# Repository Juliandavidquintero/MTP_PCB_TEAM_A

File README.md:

References:
- Connecting power button:                  https://howchoo.com/pi/how-to-add-a-power-button-to-your-raspberry-pi/
- Connecting decoupling capacitor:          https://www.mysensors.org/build/connect_radio
- Connections between module and Raspi:     https://forum.mysensors.org/topic/2437/step-by-step-procedure-to-connect-the-nrf24l01-to-the-gpio-pins-and-use-the-raspberry-as-a-serial-gateway-mysensors-1-x
                                            https://lastminuteengineers.com/nrf24l01-arduino-wireless-communication/

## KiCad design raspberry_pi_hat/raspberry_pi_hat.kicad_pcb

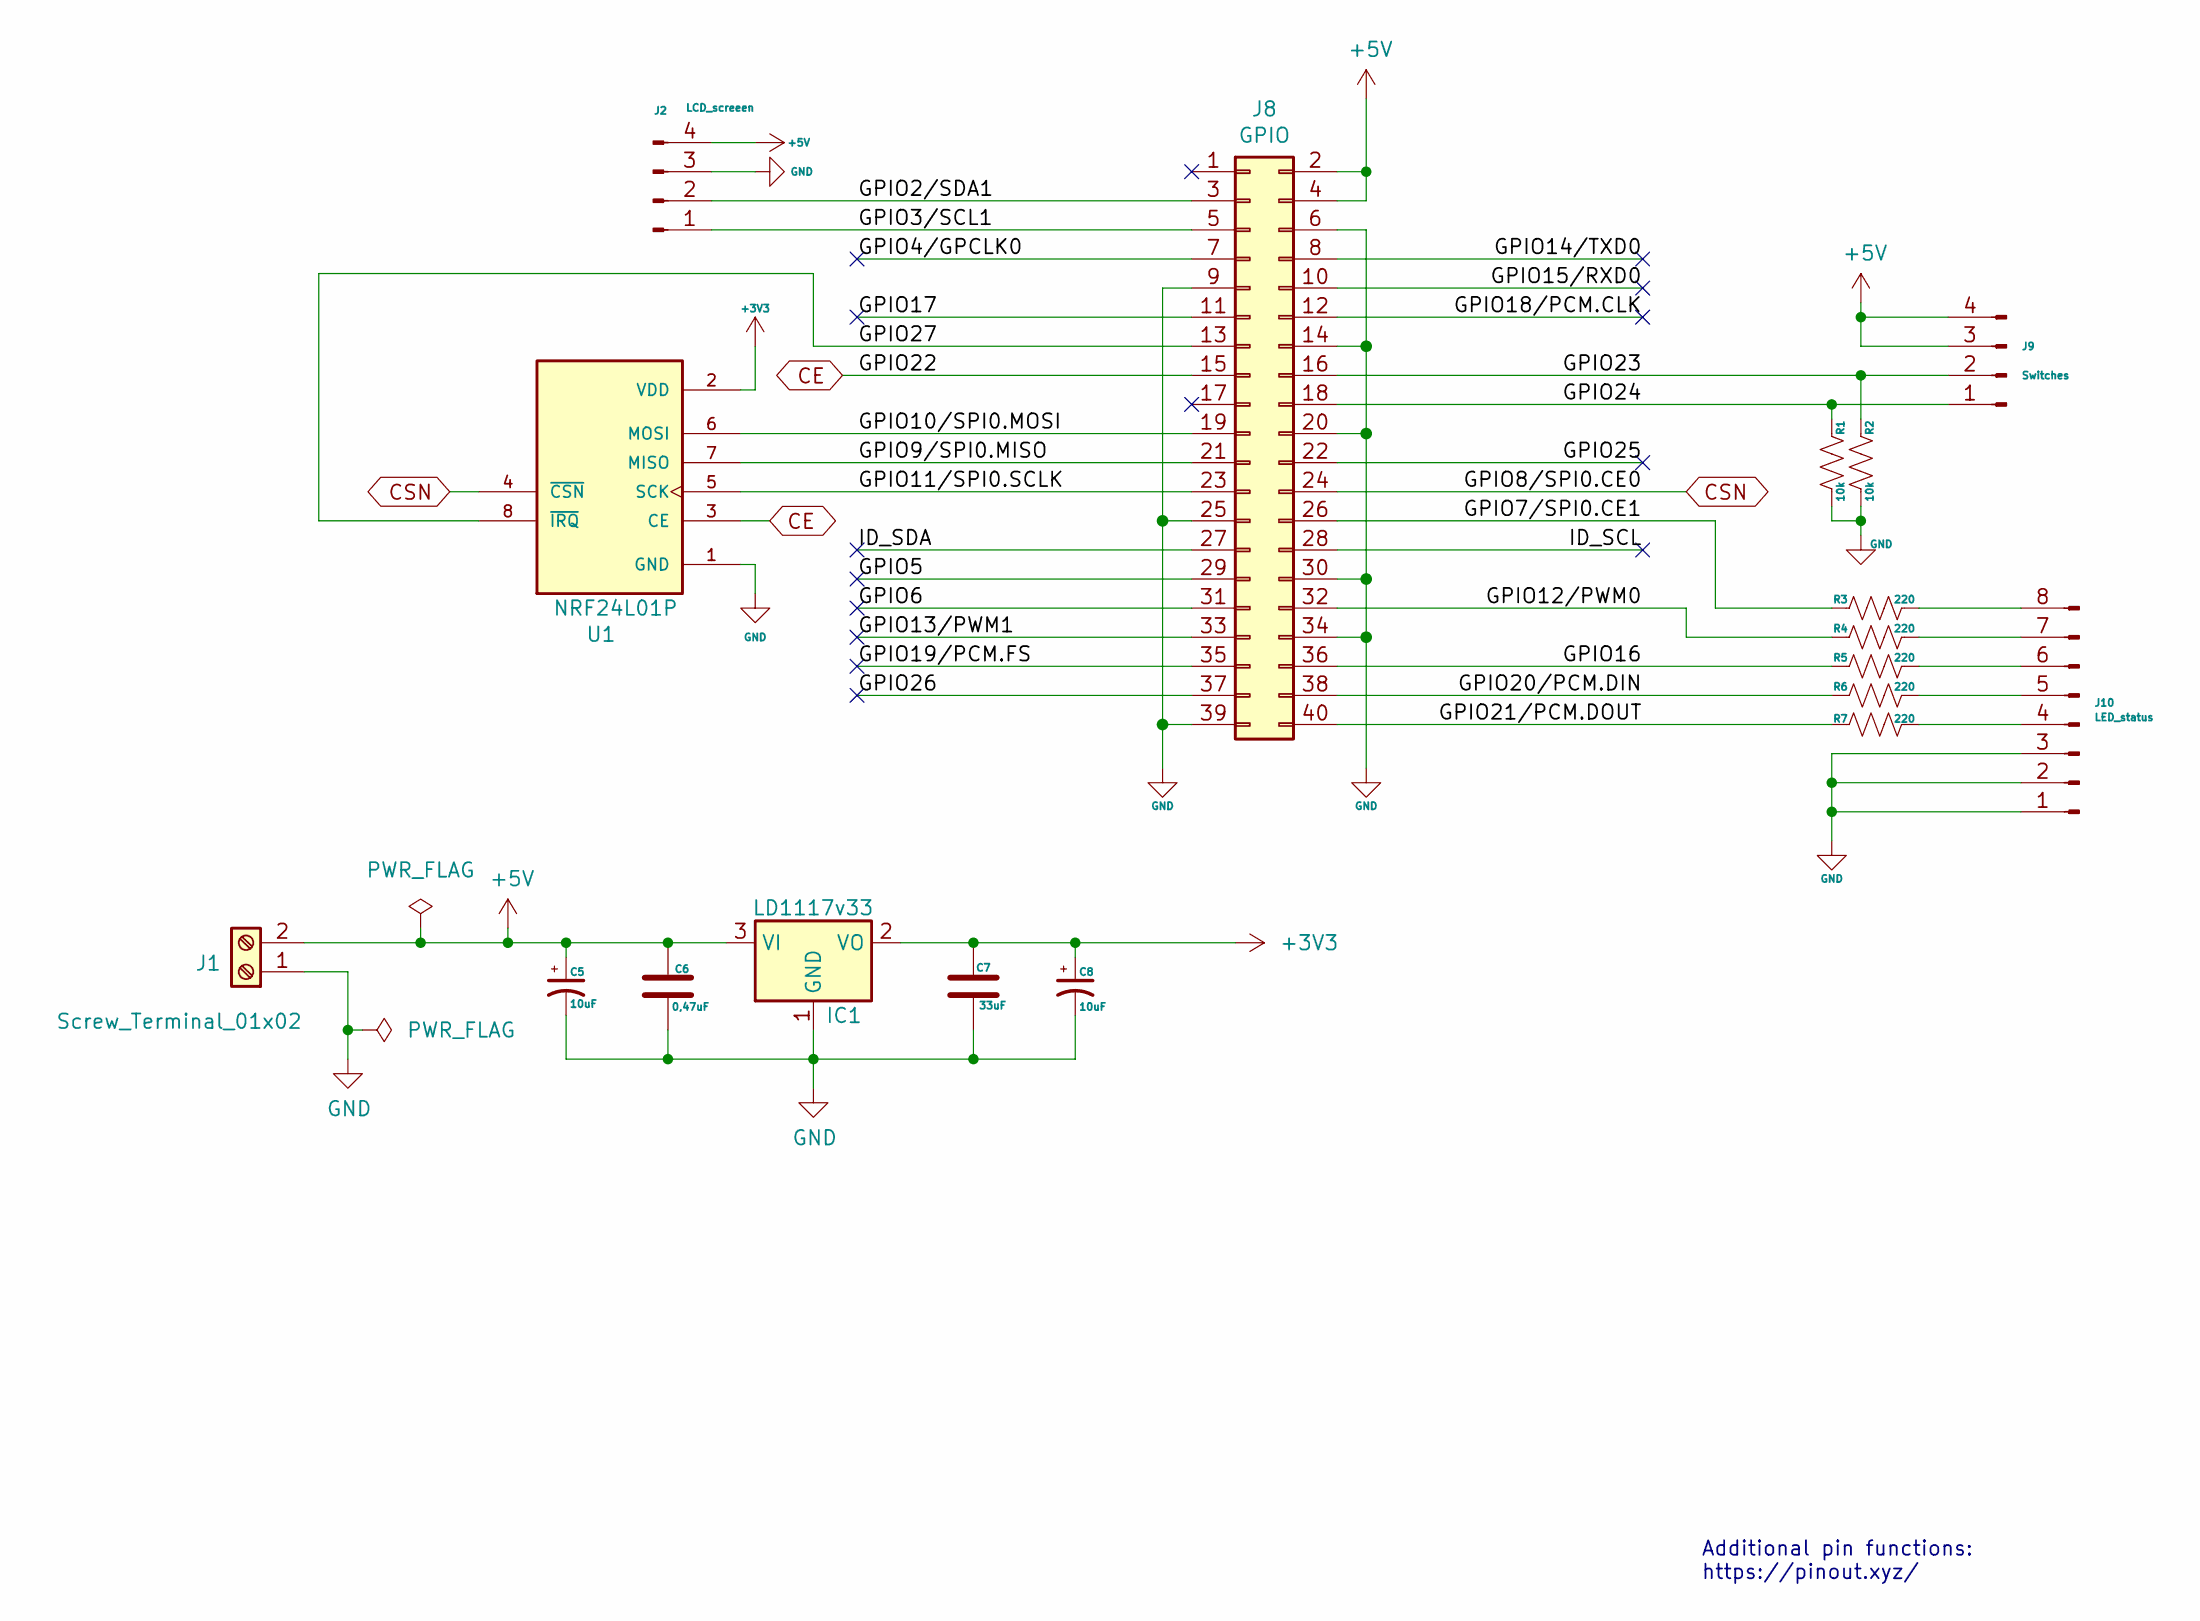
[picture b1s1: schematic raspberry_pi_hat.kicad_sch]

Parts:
C5, C8: 10uF; CP_Radial_D5.0mm_P2.50mm
C6: 0,47uF; C_Radial_D4.0mm_H5.0mm_P1.50mm
C7: 33uF; C_Radial_D4.0mm_H5.0mm_P1.50mm
IC1: LD1117v33; TO-220-3_Vertical; Mouser Part Number 926-LM3940IT-3.3NOPB
J1: Screw_Terminal_01x02; TerminalBlock_MetzConnect_Type101_RT01602HBWC_1x02_P5.08mm_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
J2: LCD_screeen; Molex_KK-254_AE-6410-04A_1x04_P2.54mm_Vertical
J8: GPIO; Raspberry_Pi_Zero_Socketed_THT_FaceDown_MountingHoles
J9: Switches; Molex_KK-254_AE-6410-04A_1x04_P2.54mm_Vertical
J10: LED_status; Molex_KK-254_AE-6410-08A_1x08_P2.54mm_Vertical
R1, R2: 10k; R_Axial_DIN0309_L9.0mm_D3.2mm_P12.70mm_Horizontal
R3, R4, R5, R6, R7: 220; R_Axial_DIN0309_L9.0mm_D3.2mm_P12.70mm_Horizontal
U1: NRF24L01P; XCVR_NRF24L01P-MODULE-PCB

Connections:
+3V3: C7.1, C8.1, IC1.2 (VO), U1.2 (VDD)
+5V: C5.1, C6.1, IC1.3 (VI), J1.2, J2.4, J8.2, J8.4, J9.3, J9.4
/GPIO2/SDA1: J2.2, J8.3
/GPIO3/SCL1: J2.1, J8.5
/GPIO4/GPCLK0: J8.7
/GPIO5: J8.29
/GPIO6: J8.31
/GPIO7/SPI0.CE1: J8.26, R3.1
/GPIO9/SPI0.MISO: J8.21, U1.7 (MISO)
/GPIO10/SPI0.MOSI: J8.19, U1.6 (MOSI)
/GPIO11/SPI0.SCLK: J8.23, U1.5 (SCK)
/GPIO12/PWM0: J8.32, R4.1
/GPIO13/PWM1: J8.33
/GPIO14/TXD0: J8.8
/GPIO15/RXD0: J8.10
/GPIO16: J8.36, R5.1
/GPIO17: J8.11
/GPIO18/PCM.CLK: J8.12
/GPIO19/PCM.FS: J8.35
/GPIO20/PCM.DIN: J8.38, R6.1
/GPIO21/PCM.DOUT: J8.40, R7.1
/GPIO23: J8.16, J9.2, R2.1
/GPIO24: J8.18, J9.1, R1.1
/GPIO25: J8.22
/GPIO26: J8.37
/GPIO27: J8.13, U1.8 (~IRQ)
/ID_SCL: J8.28
/ID_SDA: J8.27
CE: J8.15, U1.3 (CE)
CSN: J8.24, U1.4 (~CSN)
GND: C5.2, C6.2, C7.2, C8.2, IC1.1 (GND), J1.1, J2.3, J8.6, J8.9, J8.14, J8.20, J8.25, J8.30, J8.34, J8.39, J10.1, J10.2, J10.3, R1.2, R2.2, U1.1 (GND)
unnamed: J10.4, R7.2
unnamed: J10.5, R6.2
unnamed: J10.6, R5.2
unnamed: J10.7, R4.2
unnamed: J10.8, R3.2

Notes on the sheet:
Additional pin functions: https://pinout.xyz/

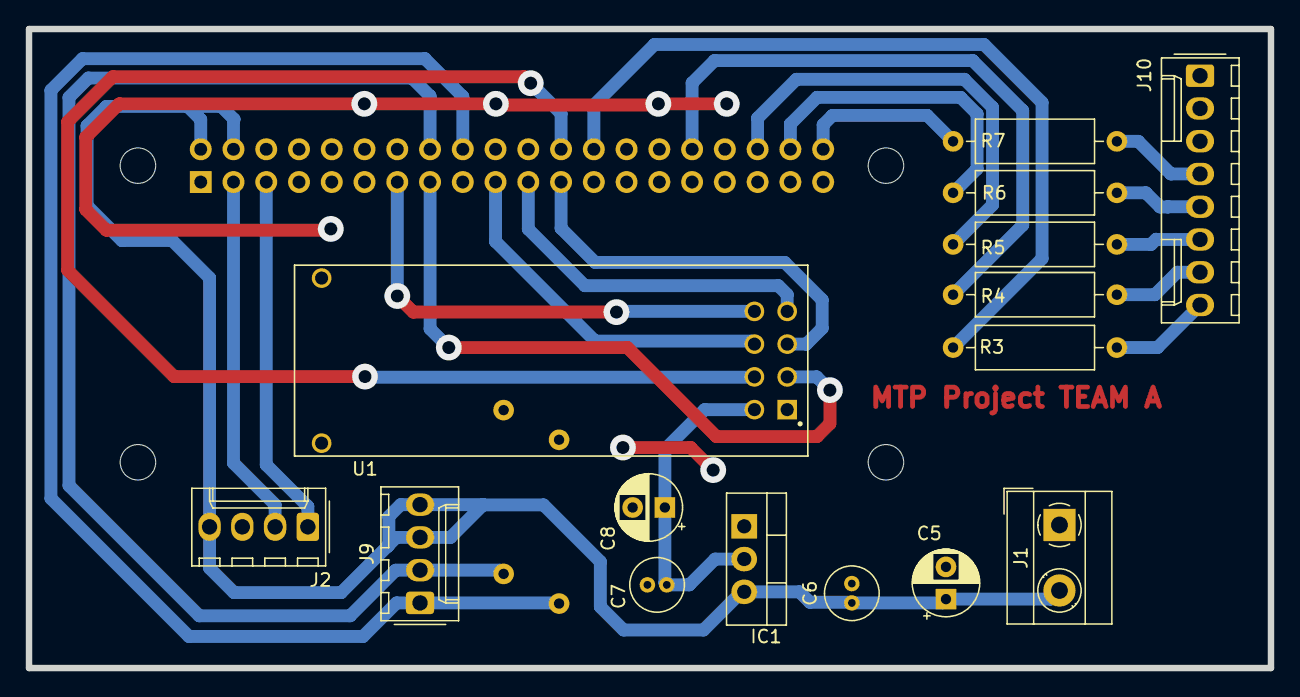
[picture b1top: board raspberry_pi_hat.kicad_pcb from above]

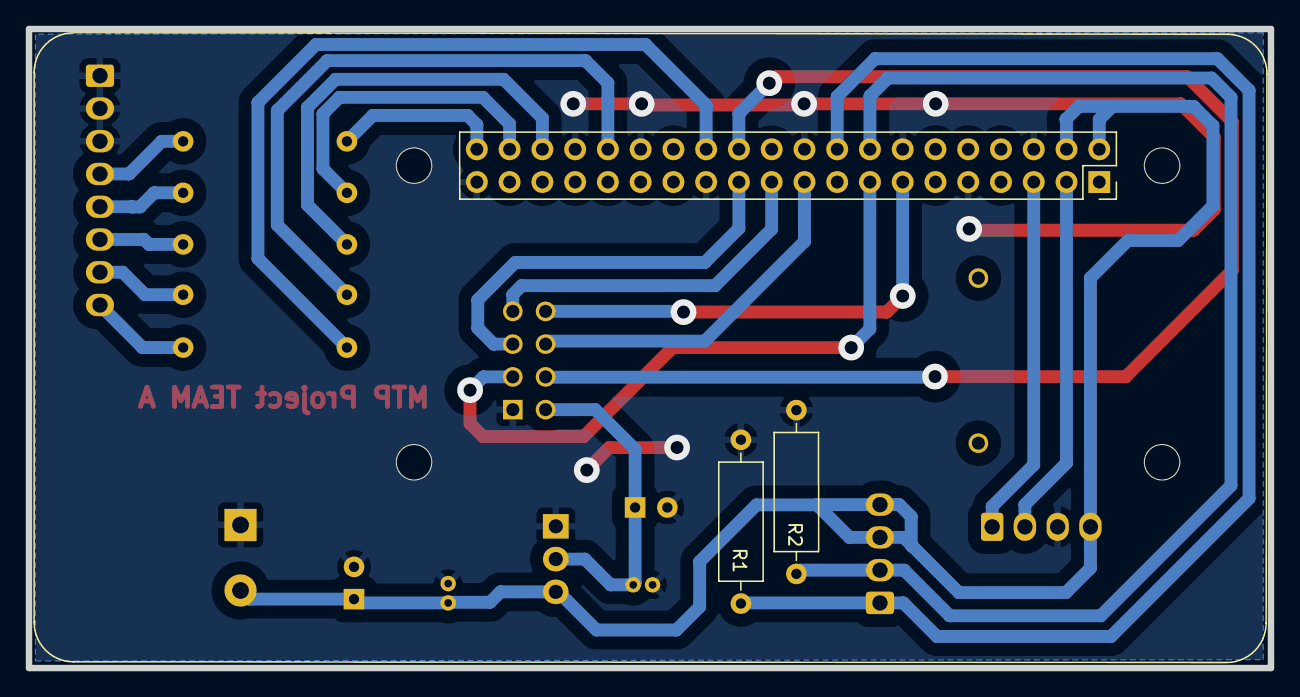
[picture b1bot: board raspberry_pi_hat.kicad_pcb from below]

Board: 2 copper layers, 96.3 x 49.5 mm, 18 parts (3 on the bottom side), 23 nets.

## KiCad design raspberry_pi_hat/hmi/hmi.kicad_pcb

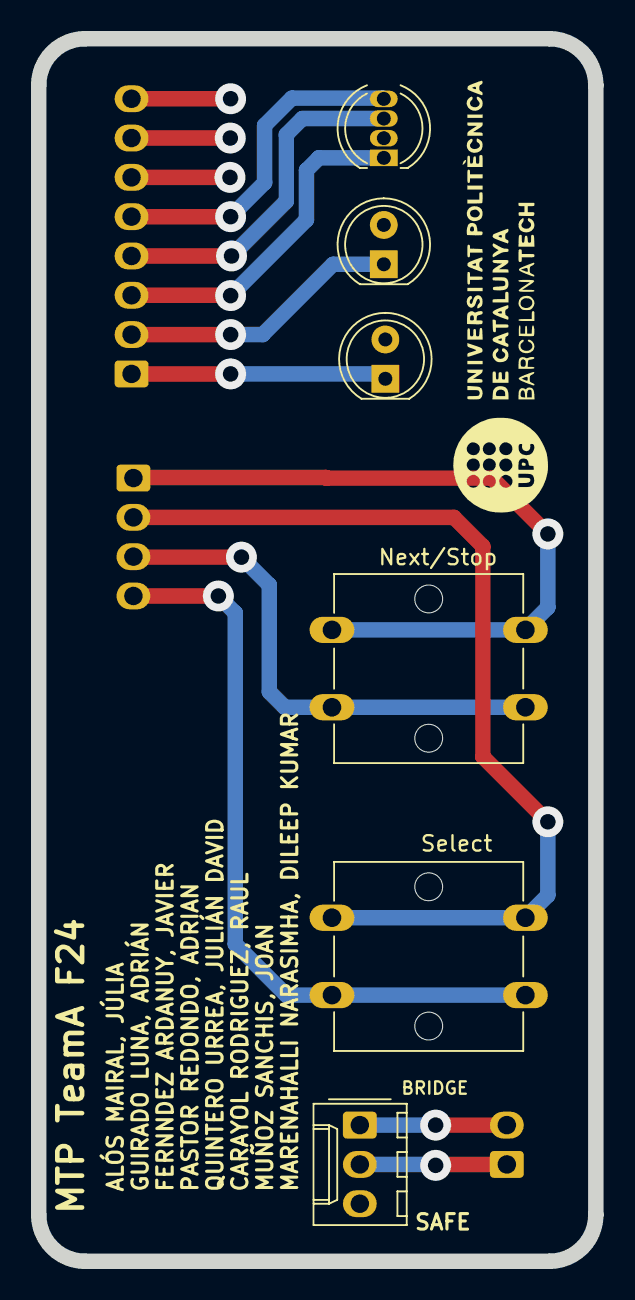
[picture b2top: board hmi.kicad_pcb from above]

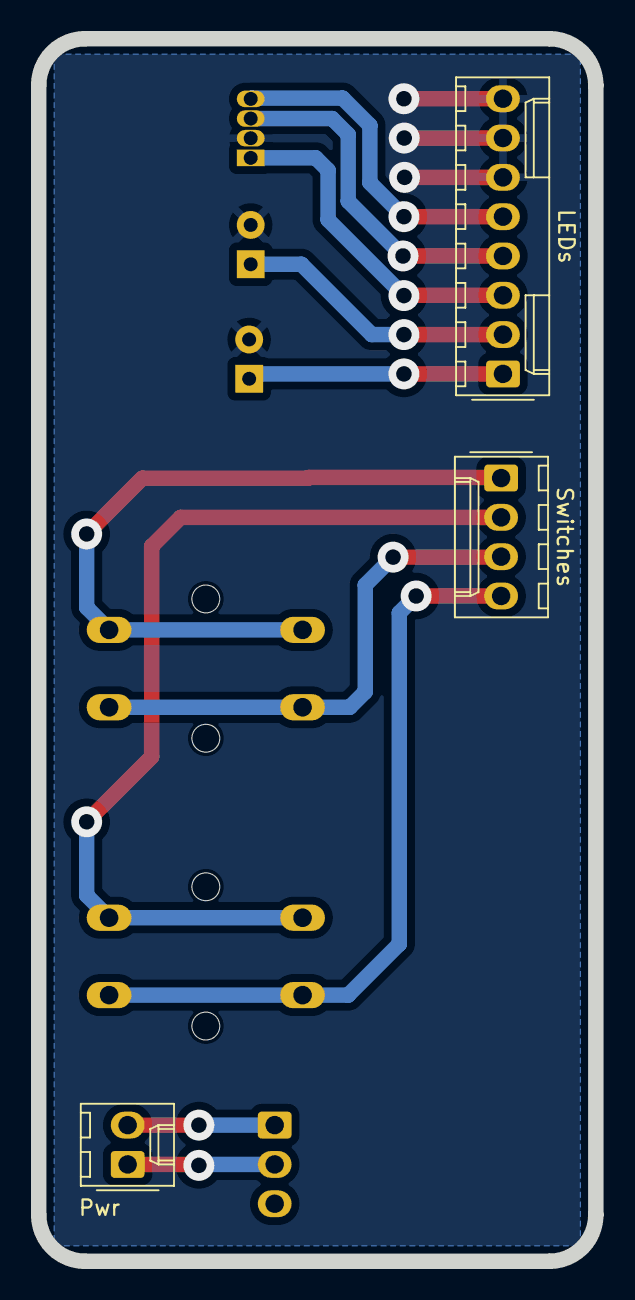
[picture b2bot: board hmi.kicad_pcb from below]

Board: 2 copper layers, 36.0 x 79.0 mm, 10 parts (3 on the bottom side), 12 nets.

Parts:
BRIDGE: Conn_01x03_Pin; Molex_KK-254_AE-6410-03A_1x03_P2.54mm_Vertical
D1_Red, D2_Green: LED; LED_D5.0mm
D3_RGB: APA-106-F5; LED_D5.0mm-4_RGB
G_logo: LOGO; UPC_logo
LEDs: Molex_KK-254_AE-6410-08A_1x08_P2.54mm_Vertical
Next/Stop: SW_Push; SW_SPST_Omron_B3F-40xx
Pwr: Conn_01x02_Pin; Molex_KK-254_AE-6410-02A_1x02_P2.54mm_Vertical
Select: SW_Push; SW_SPST_Omron_B3F-40xx
Switches: Conn_01x04_Pin; Molex_KK-254_AE-6410-04A_1x04_P2.54mm_Vertical

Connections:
GND: D1_Red.2 (A), D2_Green.2 (A), D3_RGB.2 (GND), LEDs.6, LEDs.7, LEDs.8
unnamed: D1_Red.1 (K), LEDs.1
unnamed: D2_Green.1 (K), LEDs.2
unnamed: D3_RGB.4 (DI), LEDs.5
unnamed: D3_RGB.1 (DO), LEDs.3
unnamed: D3_RGB.3 (VDD), LEDs.4
unnamed: Next/Stop.2, Switches.1
unnamed: Select.1, Switches.2
unnamed: Next/Stop.1, Switches.3
unnamed: Select.2, Switches.4
unnamed: BRIDGE.1, Pwr.2
unnamed: BRIDGE.2, Pwr.1

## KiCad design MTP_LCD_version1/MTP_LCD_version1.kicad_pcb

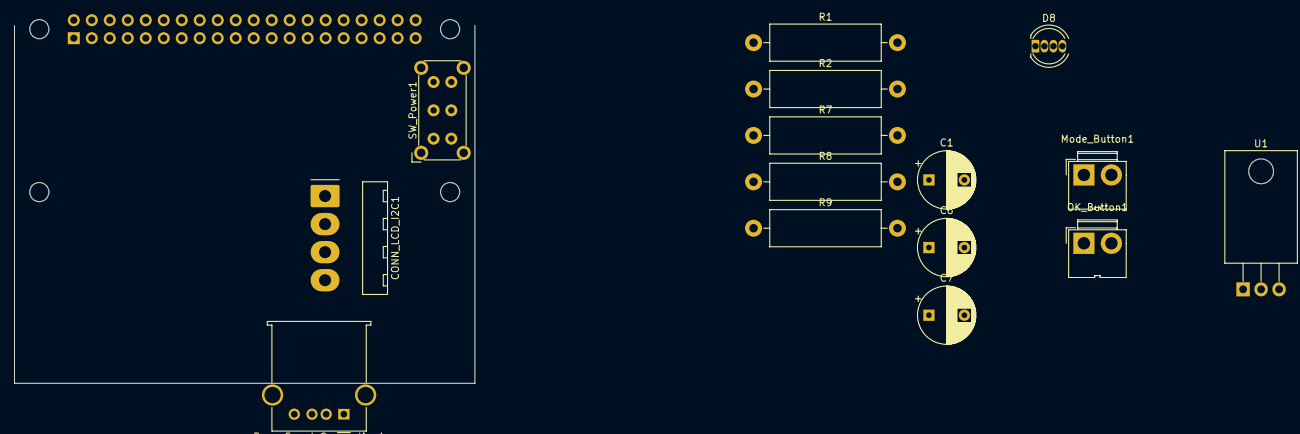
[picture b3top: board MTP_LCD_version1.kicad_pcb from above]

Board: 2 copper layers, 20 parts (1 on the bottom side), 17 nets, no tracks yet.

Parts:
C1: 47uF; CP_Radial_D8.0mm_P5.00mm
C6, C7: 10uF; CP_Radial_D8.0mm_P5.00mm
CONN_LCD_I2C1: Conn_01x04_Socket; Molex_KK-396_A-41792-0004_1x04_P3.96mm_Horizontal
D8: LED_KRGB; LED_D5.0mm-4_RGB
J1: GPIO; PinSocket_2x20_P2.54mm_Vertical
MH1, MH2, MH3, MH4: MountingHole_2.7mm_M2.5
Mode_Button1: Conn_01x02_Pin; JWT_A3963_1x02_P3.96mm_Vertical
OK_Button1: Conn_01x02_Pin; JWT_A3963_1x02_P3.96mm_Vertical
PowerSupplyConnection1: USB_A; USB_A_Molex_67643_Horizontal
R1, R2, R7, R8, R9: 220; R_Axial_DIN0516_L15.5mm_D5.0mm_P20.32mm_Horizontal
SW_Power1: SW_DPDT_x2; SW_E-Switch_EG2219_DPDT_Angled
U1: LM1117T-2.5; TO-220-3_Horizontal_TabDown

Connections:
+3V3: C7.1, U1.2 (VO)
/GPIO12/PWM0: J1.32, R8.1
/GPIO16: J1.36, R2.1
/GPIO20/PCM.DIN: J1.38, R1.1
/GPIO21/PCM.DOUT: J1.40, R7.1
BLUE_LED: J1.37, R9.1
GND: C1.2, C6.2, C7.2, CONN_LCD_I2C1.1, D8.1 (K), J1.6, J1.9, J1.14, J1.20, J1.25, J1.30, J1.34, J1.39, PowerSupplyConnection1.4 (GND), U1.1 (GND)
Mode_Button_input: J1.16, Mode_Button1.1
unnamed: D8.4 (BA), R9.2
unnamed: D8.3 (GA), R8.2
unnamed: D8.2 (RA), R2.2
unnamed: J1.1, J1.17
unnamed: PowerSupplyConnection1.1 (VBUS), SW_Power1.2 (B)
OK_Button_input: J1.18, OK_Button1.1
SCL: CONN_LCD_I2C1.4, J1.5
SDA: CONN_LCD_I2C1.3, J1.3
VCC: C1.1, C6.1, CONN_LCD_I2C1.2, J1.2, J1.4, Mode_Button1.2, OK_Button1.2, SW_Power1.3 (C), U1.3 (VI)

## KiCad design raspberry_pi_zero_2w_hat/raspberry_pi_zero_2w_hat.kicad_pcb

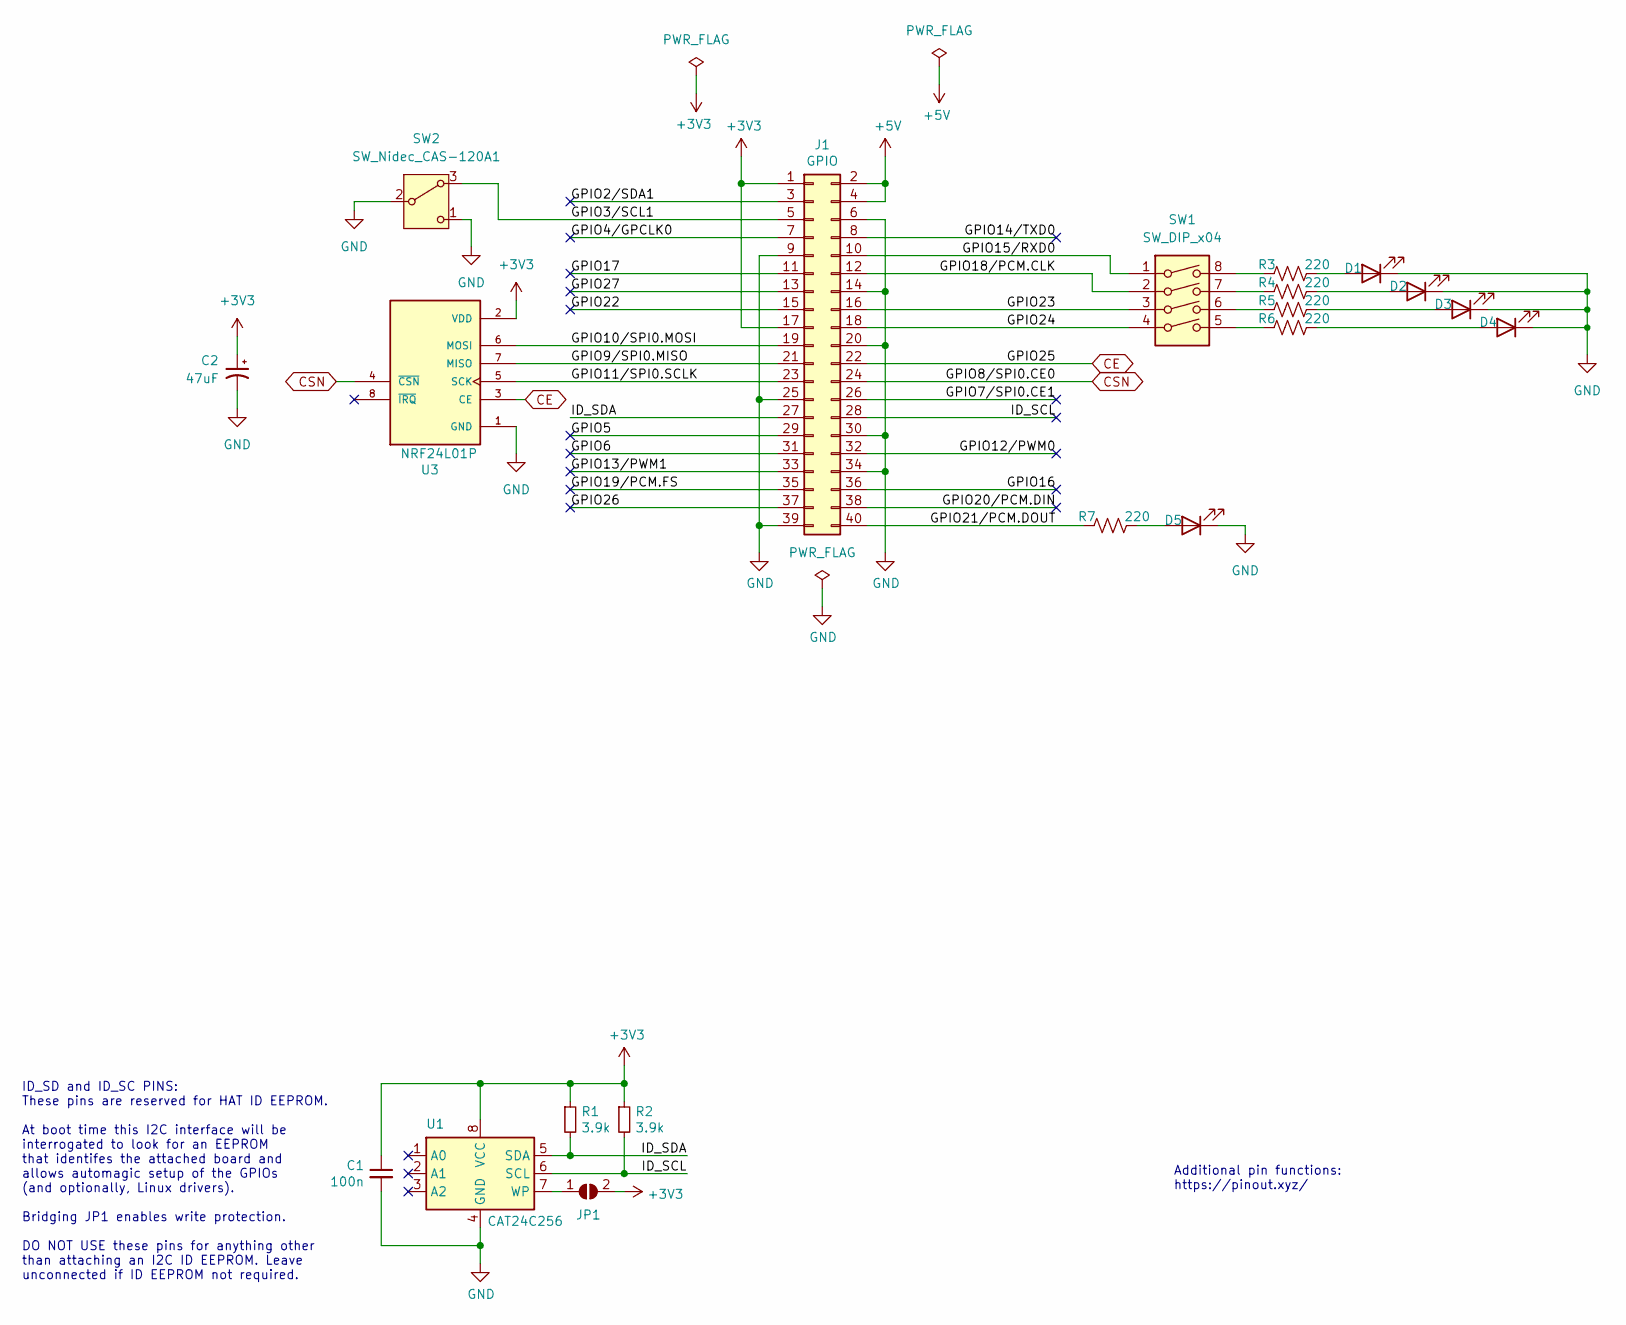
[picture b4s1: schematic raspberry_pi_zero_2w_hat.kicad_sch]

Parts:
C1: 100n
C2: 47uF; CP_Radial_D8.0mm_P5.00mm
D1: LED; LED_D5.0mm_Horizontal_O1.27mm_Z3.0mm
D2, D3, D4, D5: LED
J1: GPIO; PinSocket_2x20_P2.54mm_Vertical
JP1: ID_WP
R1, R2: 3.9k
R3, R4, R5, R6, R7: 220; R_Axial_DIN0516_L15.5mm_D5.0mm_P20.32mm_Horizontal
SW1: SW_DIP_x04
SW2: SW_Nidec_CAS-120A1; SW_SPST_Omron_B3FS-100xP
U1: CAT24C256
U3: NRF24L01P

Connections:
+3V3: C1.1, C2.1, J1.1, J1.17, JP1.2 (B), R1.1, R2.1, U1.8 (VCC), U3.2 (VDD)
+5V: J1.2, J1.4
/GPIO2/SDA1: J1.3
/GPIO4/GPCLK0: J1.7
/GPIO5: J1.29
/GPIO6: J1.31
/GPIO7/SPI0.CE1: J1.26
/GPIO9/SPI0.MISO: J1.21, U3.7 (MISO)
/GPIO10/SPI0.MOSI: J1.19, U3.6 (MOSI)
/GPIO11/SPI0.SCLK: J1.23, U3.5 (SCK)
/GPIO12/PWM0: J1.32
/GPIO13/PWM1: J1.33
/GPIO14/TXD0: J1.8
/GPIO15/RXD0: J1.10, SW1.1
/GPIO16: J1.36
/GPIO17: J1.11
/GPIO18/PCM.CLK: J1.12, SW1.2
/GPIO19/PCM.FS: J1.35
/GPIO20/PCM.DIN: J1.38
/GPIO21/PCM.DOUT: J1.40, R7.1
/GPIO22: J1.15
/GPIO23: J1.16, SW1.3
/GPIO24: J1.18, SW1.4
/GPIO26: J1.37
/GPIO27: J1.13
/ID_SCL: J1.28, R2.2, U1.6 (SCL)
/ID_SDA: J1.27, R1.2, U1.5 (SDA)
CE: J1.22, U3.3 (CE)
CSN: J1.24, U3.4 (~CSN)
unnamed: D1.2 (A), R3.2
unnamed: D2.2 (A), R4.2
unnamed: D3.2 (A), R5.2
unnamed: D4.2 (A), R6.2
unnamed: D5.2 (A), R7.2
unnamed: JP1.1 (A), U1.7 (WP)
unnamed: R3.1, SW1.8
unnamed: R4.1, SW1.7
unnamed: R5.1, SW1.6
unnamed: R6.1, SW1.5

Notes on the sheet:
ID_SD and ID_SC PINS: These pins are reserved for HAT ID EEPROM. At boot time this I2C interface will be interrogated to look for an EEPROM that identifes the attached board and allows automagic setup of the GPIOs (and optionally, Linux drivers). Bridging JP1 enables write protection. DO NOT USE th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
Additional pin functions: https://pinout.xyz/

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
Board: 2 copper layers, 24 parts (1 on the bottom side), 26 nets, no tracks yet.

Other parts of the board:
MH1, MH2, MH3, MH4: MountingHole_2.7mm_M2.5

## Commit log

2024-09-26 first project commit
2024-10-02 changed hat format to fit raspberry pi w format
2024-10-02 cleaning cache
2024-10-02 cleaning wrong files
2024-10-03 Added symbol and footprint libraries, connected rf module to hat in schematcs
2024-10-03 Added decoupling capacitor for transceiver module
2024-10-03 Added On-Off switch
2024-10-03 Added status dipswuitch to schematics
2024-10-03 Added transmission LED to schematics
2024-10-03 Create README.md
    References and utility sources
2024-10-03 ERC errors solved
2024-10-04 Added symbols, footprints and first layout
2024-10-11 First approach to the schematic with lcd connector
2024-10-12 splitted into 2 pcbs
2024-10-14 Adding USB power connector
2024-10-15 improving schematics to fit layout requirements
2024-10-15 Solved split connection issues between boards
2024-10-15 Solved connection issues and THT routing
2024-10-15 Added RF module 3D model
2024-10-15 corrected positions
2024-10-17 Updated PCBs with professor changes to make first sample
2024-10-30 Changed boards orientation and redistribution of components, still being 2 boards
2024-11-01 Completed redistribution of boards
2024-11-01 Combined both PCBs successfully and solved errors
2024-12-19 improved final version
